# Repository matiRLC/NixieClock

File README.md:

View this project on [CADLAB.io](https://cadlab.io/project/1200). 

# NixieClock
Nixie Tube Clock based project based on existing code and boards by Ogilumen and RobotPirate

The current project uses an Arduino Uno and the Arduinix Shield from RobotPirate. The code is an extension of the sample code
provided by the latter. The PCB for 6 nixie tubes was designed based on the .pdf schematic available in [Arduinix](http://www.arduinix.com).

As of 2019, the current design uses a bluetooth module (HC-06 or HM-10). The use of HM-10 was chosen since it's a Bluetooth 4.0+ module that allows it to work with both Android and iOS apps.

The iOS app was implemented with the work from [hoiberg](https://github.com/hoiberg/HM10-BluetoothSerial-iOS) as a template. His explanation of his project can be found [here](http://www.hangar42.nl/hm10).

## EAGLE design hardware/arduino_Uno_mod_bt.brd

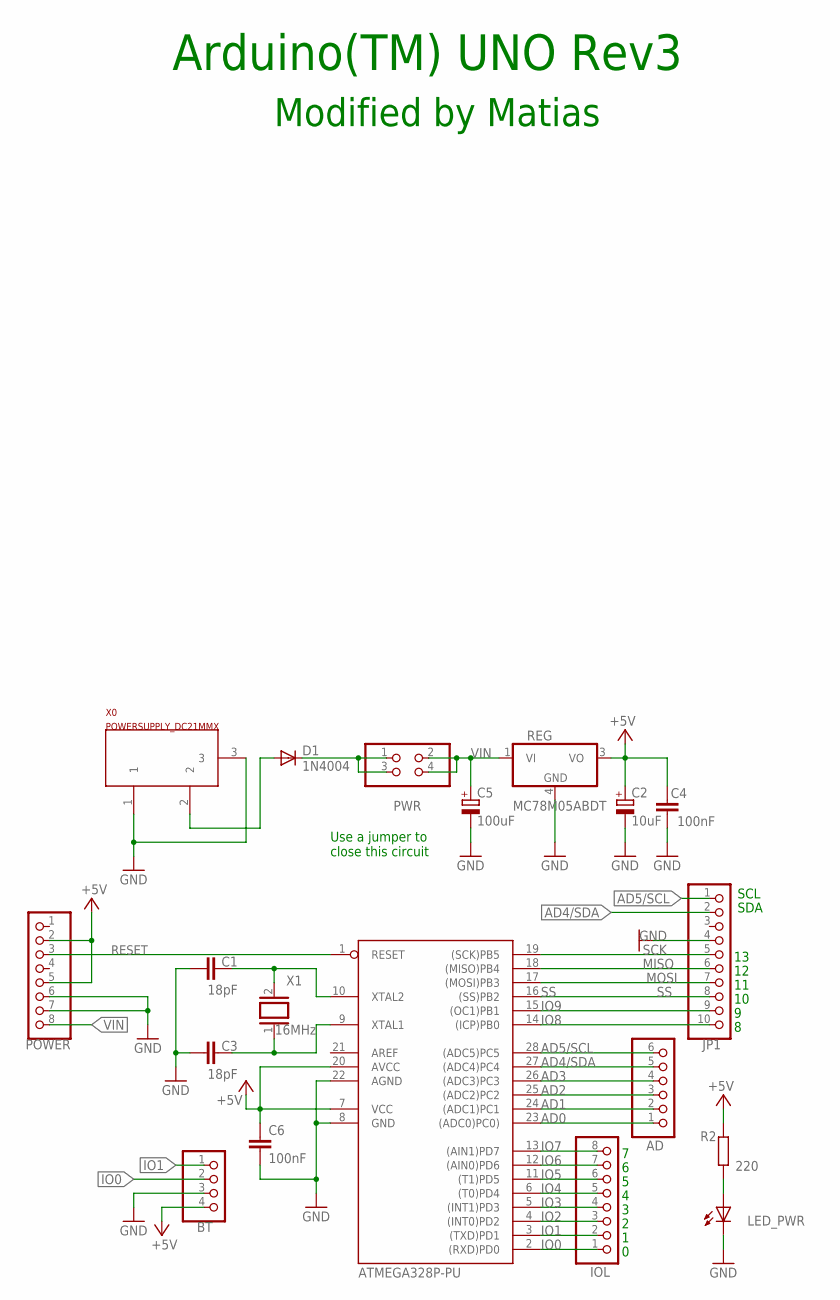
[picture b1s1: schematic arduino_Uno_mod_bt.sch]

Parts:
AD: 6x1F-H8.5; 1X06
BT: PINHD-1X4/90; 1X04/90
C1, C3: 18pF; C025-025X050
C2: 10uF; E2,5-5
C4, C6: 100nF; C025-025X050
C5: 100uF; E2-5
D1: 1N4004; DO41-10
IOL: 8x1F-H8.5; 1X08
JP1: PINHD-1X10; 1X10
LED_PWR: LED3MM
POWER: 8x1F-H8.5; 1X08
PWR: PINHD-2X2; 2X02
R2: 220; R1206
REG: MC78M05ABDT; DPACK_3
X0: POWERSUPPLY_DC21MMX; POWERSUPPLY_DC-21MM
X1: 16MHz; QS
ZU4: ATMEGA328P-PU; DIL28-3

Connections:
+5V: BT.4, C2.+, C4.2, C6.1, POWER.2, POWER.5, R2.2, REG.3 (VO), ZU4.7 (VCC), ZU4.20 (AVCC)
AD0: AD.1, ZU4.23 ((ADC0)PC0))
AD1: AD.2, ZU4.24 ((ADC1)PC1)
AD2: AD.3, ZU4.25 ((ADC2)PC2)
AD3: AD.4, ZU4.26 ((ADC3)PC3)
AD4/SDA: AD.5, JP1.2, ZU4.27 ((ADC4)PC4)
AD5/SCL: AD.6, JP1.1, ZU4.28 ((ADC5)PC5)
GND: BT.3, C1.1, C2.-, C3.1, C4.1, C5.-, C6.2, JP1.4, LED_PWR.K (C), POWER.6, POWER.7, REG.4 (GND), X0.1, X0.3, ZU4.8 (GND), ZU4.22 (AGND)
IN: D1.A, X0.2
IO0: BT.2, IOL.1, ZU4.2 ((RXD)PD0)
IO1: BT.1, IOL.2, ZU4.3 ((TXD)PD1)
IO2: IOL.3, ZU4.4 ((INT0)PD2)
IO3: IOL.4, ZU4.5 ((INT1)PD3)
IO4: IOL.5, ZU4.6 ((T0)PD4)
IO5: IOL.6, ZU4.11 ((T1)PD5)
IO6: IOL.7, ZU4.12 ((AIN0)PD6)
IO7: IOL.8, ZU4.13 ((AIN1)PD7)
IO8: JP1.10, ZU4.14 ((ICP)PB0)
IO9: JP1.9, ZU4.15 ((OC1)PB1)
MISO: JP1.6, ZU4.18 ((MISO)PB4)
MOSI: JP1.7, ZU4.17 ((MOSI)PB3)
unnamed: C3.2, X1.1, ZU4.9 (XTAL1)
unnamed: LED_PWR.A, R2.1
unnamed: D1.C, PWR.1, PWR.3
RESET: POWER.3, ZU4.1 (RESET)
SCK: JP1.5, ZU4.19 ((SCK)PB5)
SS: JP1.8, ZU4.16 ((SS)PB2)
VIN: C5.+, POWER.8, PWR.2, PWR.4, REG.1 (VI)
XTAL2: C1.2, X1.2, ZU4.10 (XTAL2)

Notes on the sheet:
Arduino(TM) UNO Rev3
SDA
SCL
Modified by Matias
Use a jumper to close this circuit

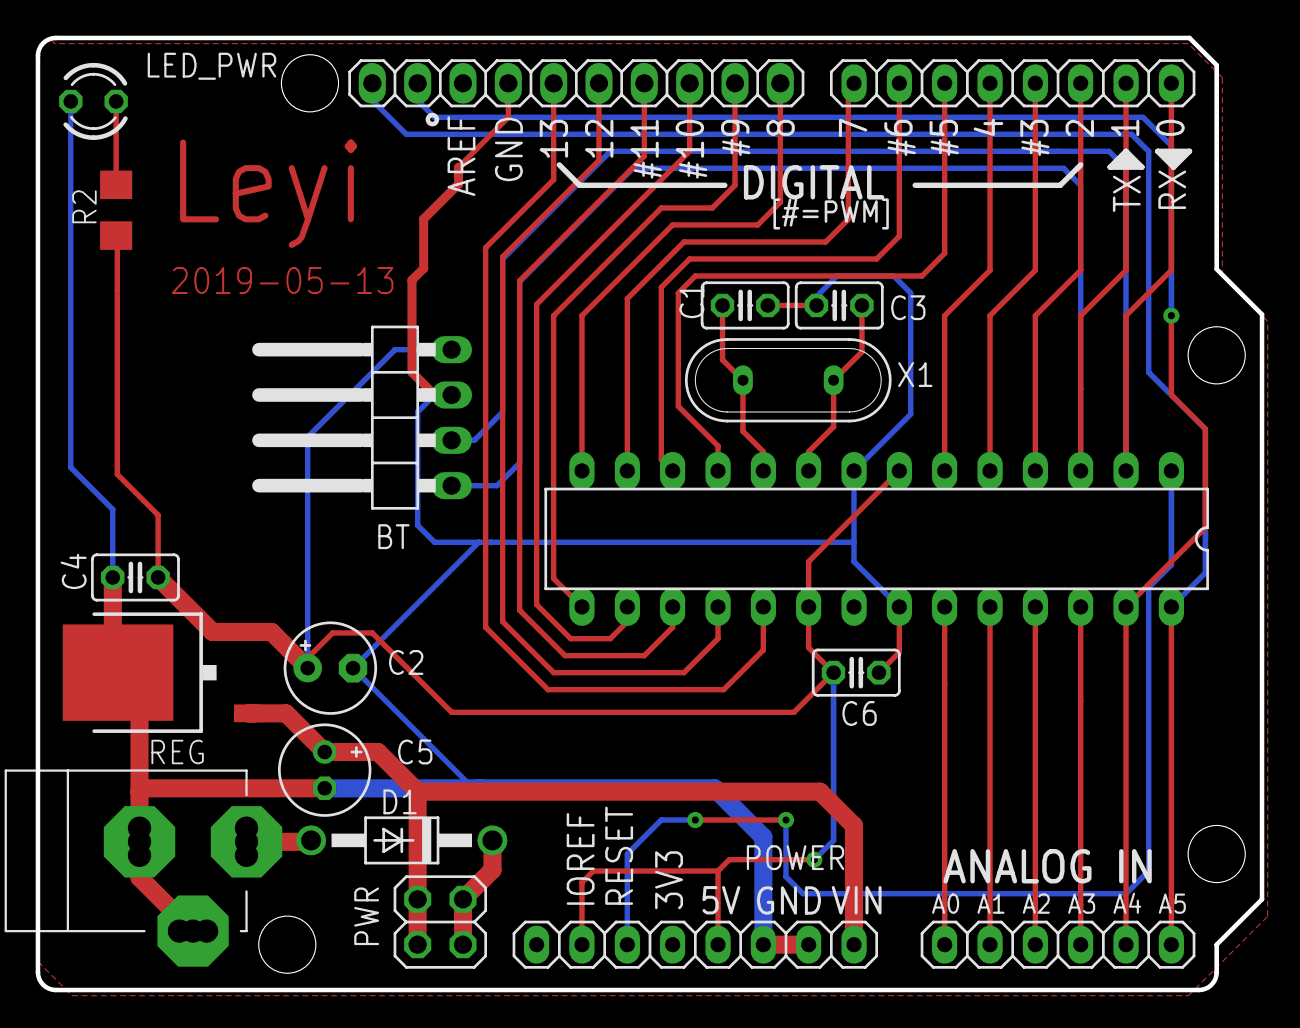
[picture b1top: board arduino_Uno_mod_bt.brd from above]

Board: 2 copper layers, 68.6 x 53.3 mm, 19 parts (0 on the bottom side), 29 nets.

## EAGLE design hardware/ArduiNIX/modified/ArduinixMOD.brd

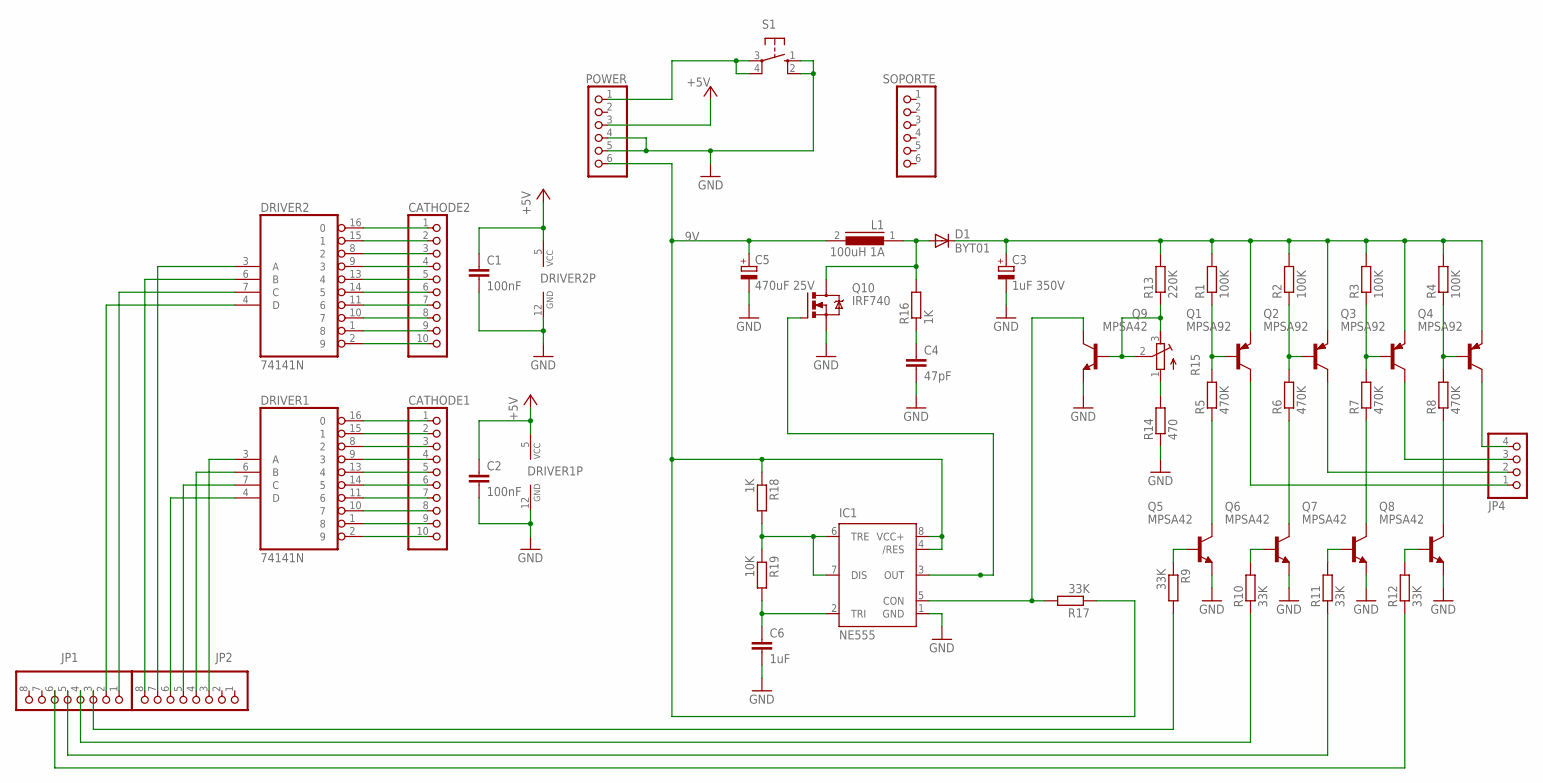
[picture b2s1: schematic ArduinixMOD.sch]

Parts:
C1, C2: 100nF; C025-025X050
C3: 1uF 350V; E2,5-7
C4: 47pF; C025-025X050
C5: 470uF 25V; E5-10,5
C6: 1uF; C025-025X050
CATHODE1, CATHODE2: PINHD-1X10; 1X10
D1: BYT01; F126-10
DRIVER1, DRIVER2: 74141N; DIL16
IC1: NE555; DIL-08
JP1, JP2: PINHD-1X8; 1X08
JP4: PINHD-1X4; 1X04
L1: 100uH 1A; MESC26
POWER: PINHD-1X6; 1X06
Q1, Q2, Q3, Q4: MPSA92; TO92-CBE
Q5, Q6, Q7, Q8, Q9: MPSA42; TO92-EBC
Q10: IRF740; TO220BV
R1, R2, R3, R4: 100K; R1206
R5, R6, R7, R8: 470K; R1206
R9, R10, R11, R12, R17: 33K; R1206
R13: 220K; R1206
R14: 470; R1206
R15: R-TRIMM64W; RTRIM64W
R16, R18: 1K; R1206
R19: 10K; R1206
S1: 10-XX; B3F-10XX
SOPORTE: PINHD-1X6; 1X06

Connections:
9V: C5.+, IC1.4 (/RES), IC1.8 (VCC+), L1.2, POWER.6, R17.1, R18.1
+5V: C1.1, C2.1, DRIVER1.5 (VCC), DRIVER2.5 (VCC), POWER.3
GND: C1.2, C2.2, C3.-, C4.2, C5.-, C6.2, DRIVER1.12 (GND), DRIVER2.12 (GND), IC1.1 (GND), POWER.4, POWER.5, Q5.E, Q6.E, Q7.E, Q8.E, Q9.E, Q10.S, R14.1, S1.1 (S), S1.2 (S1)
unnamed: CATHODE2.9, DRIVER2.1 (8)
unnamed: CATHODE2.10, DRIVER2.2 (9)
unnamed: DRIVER2.3 (A), JP2.7
unnamed: DRIVER2.4 (D), JP1.2
unnamed: DRIVER2.6 (B), JP2.8
unnamed: DRIVER2.7 (C), JP1.1
unnamed: CATHODE2.3, DRIVER2.8 (2)
unnamed: CATHODE2.4, DRIVER2.9 (3)
unnamed: CATHODE2.8, DRIVER2.10 (7)
unnamed: CATHODE2.7, DRIVER2.11 (6)
unnamed: DRIVER1.4 (D), JP2.6
unnamed: CATHODE2.5, DRIVER2.13 (4)
unnamed: CATHODE2.6, DRIVER2.14 (5)
unnamed: CATHODE2.2, DRIVER2.15 (1)
unnamed: CATHODE2.1, DRIVER2.16 (0)
unnamed: DRIVER1.6 (B), JP2.4
unnamed: DRIVER1.7 (C), JP2.5
unnamed: CATHODE1.3, DRIVER1.8 (2)
unnamed: CATHODE1.9, DRIVER1.1 (8)
unnamed: CATHODE1.10, DRIVER1.2 (9)
unnamed: DRIVER1.3 (A), JP2.3
unnamed: CATHODE1.4, DRIVER1.9 (3)
unnamed: CATHODE1.8, DRIVER1.10 (7)
unnamed: CATHODE1.7, DRIVER1.11 (6)
unnamed: CATHODE1.5, DRIVER1.13 (4)
unnamed: CATHODE1.6, DRIVER1.14 (5)
unnamed: CATHODE1.2, DRIVER1.15 (1)
unnamed: CATHODE1.1, DRIVER1.16 (0)
unnamed: Q1.B, R1.1, R5.2
unnamed: Q2.B, R2.1, R6.2
unnamed: Q3.B, R3.1, R7.2
unnamed: Q4.B, R4.1, R8.2
unnamed: D1.A, L1.1, Q10.D, R16.2
unnamed: JP4.2, Q2.C
unnamed: JP1.3, R9.2
unnamed: JP4.1, Q1.C
unnamed: JP1.4, R10.1
unnamed: JP4.3, Q3.C
unnamed: JP4.4, Q4.C
unnamed: Q5.C, R5.1
unnamed: Q6.C, R6.1
unnamed: Q5.B, R9.1
unnamed: Q6.B, R10.2
unnamed: Q7.B, R11.2
unnamed: Q7.C, R7.1
unnamed: Q8.C, R8.1
unnamed: Q8.B, R12.2
unnamed: JP1.5, R11.1
unnamed: JP1.6, R12.1
unnamed: Q9.B, R13.1, R15.2 (S), R15.3 (E)
unnamed: C4.1, R16.1
unnamed: R14.2, R15.1 (A)
unnamed: C3.+, D1.C, Q1.E, Q2.E, Q3.E, Q4.E, R1.2, R2.2, R3.2, R4.2, R13.2
unnamed: IC1.6 (TRE), IC1.7 (DIS), R18.2, R19.1
unnamed: C6.1, IC1.2 (TRI), R19.2
unnamed: POWER.1, S1.3, S1.4 (P1)
unnamed: IC1.5 (CON), Q9.C, R17.2
unnamed: IC1.3 (OUT), Q10.G

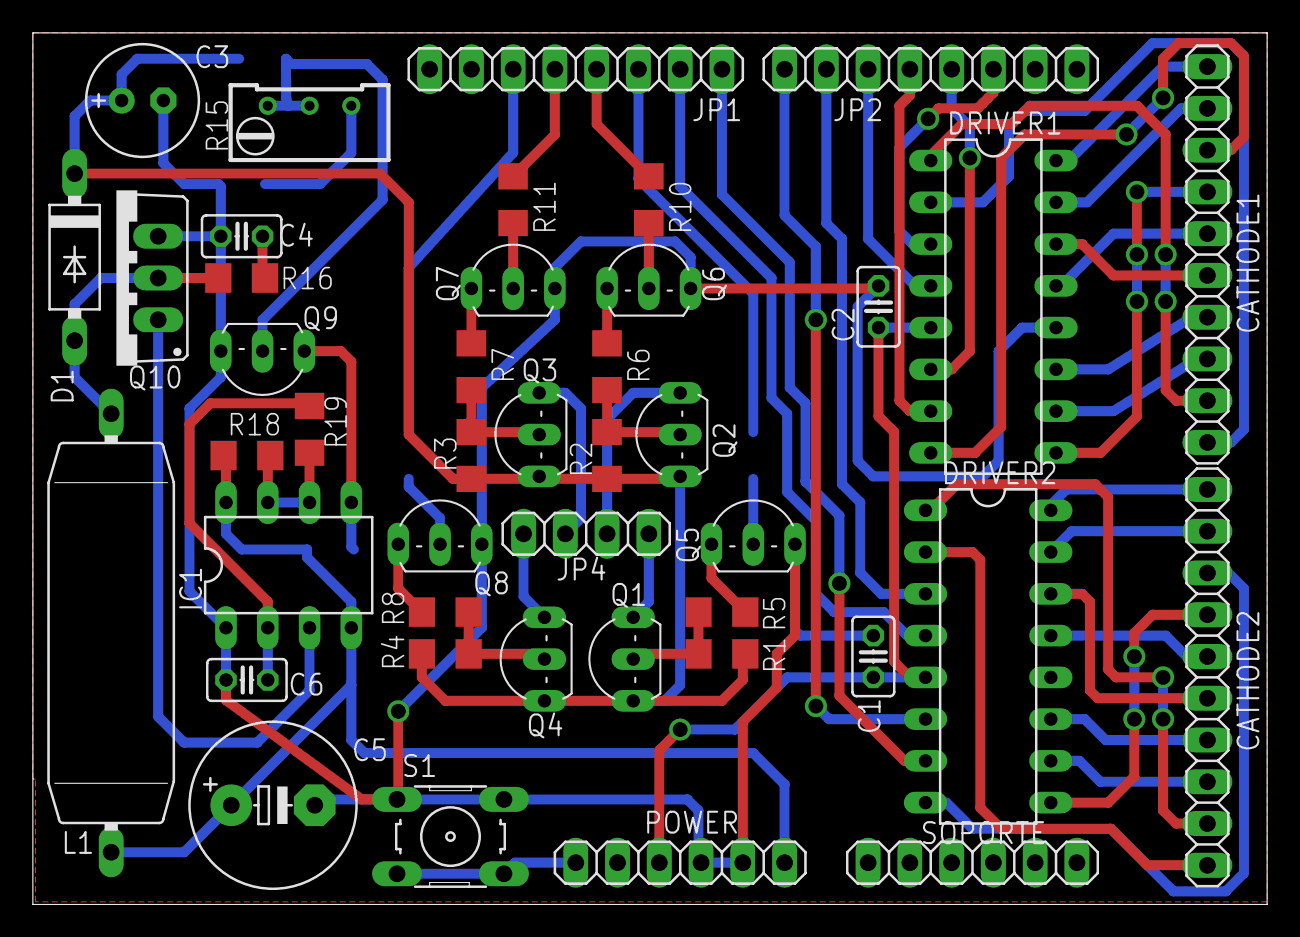
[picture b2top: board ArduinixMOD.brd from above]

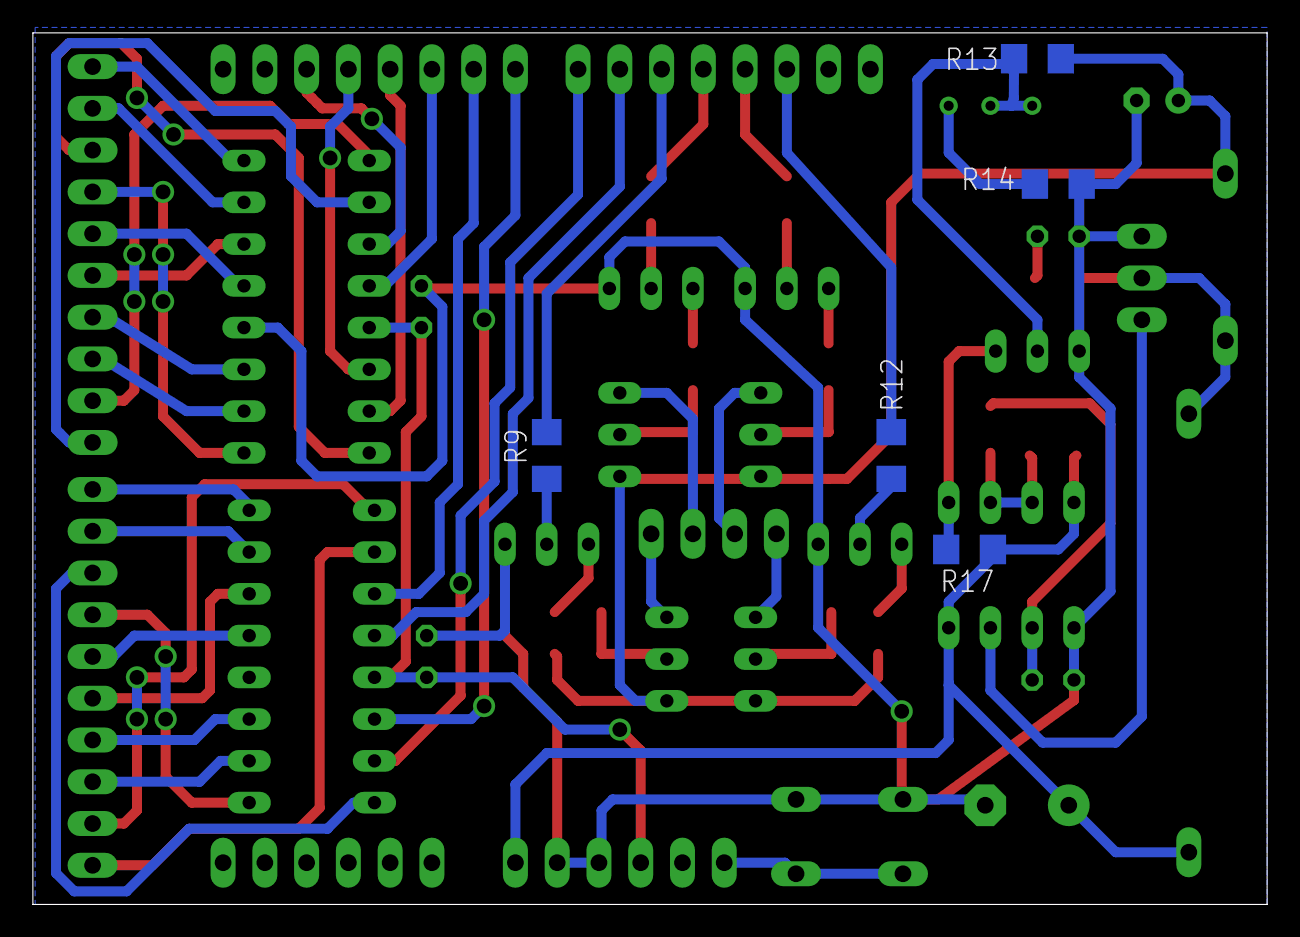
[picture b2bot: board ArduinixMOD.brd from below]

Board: 2 copper layers, 75.1 x 53.0 mm, 48 parts (5 on the bottom side), 61 nets.

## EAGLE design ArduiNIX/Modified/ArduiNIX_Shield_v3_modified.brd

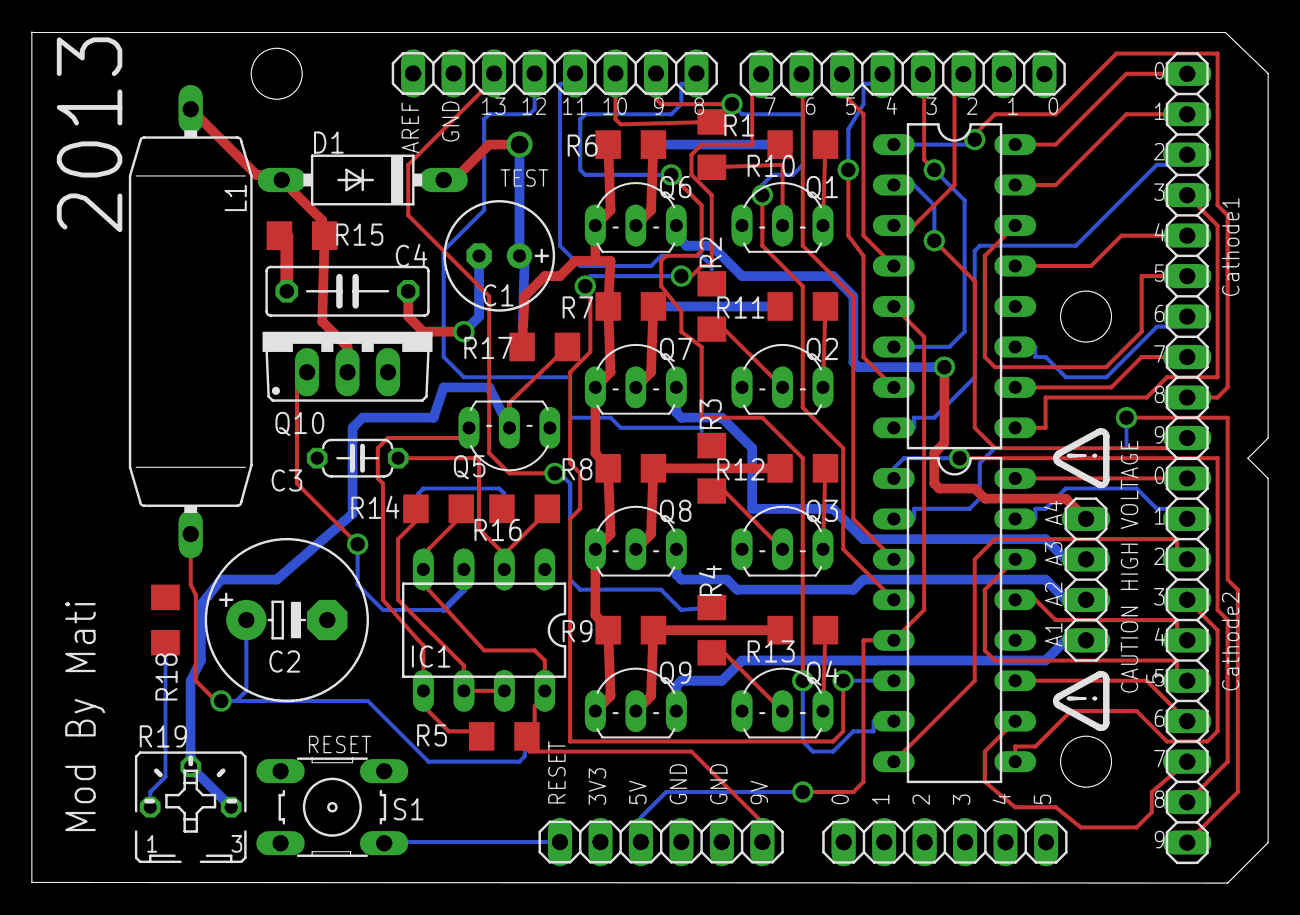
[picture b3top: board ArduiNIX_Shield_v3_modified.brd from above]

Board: 2 copper layers, 77.6 x 53.4 mm, 46 parts (0 on the bottom side), 61 nets.

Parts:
C1: 1uF 350v; E2,5-7
C2: 470uF 25v; E5-10,5
C3: 2n2; C050-024X044
C4: 47pF; C075-032X103
CATHODE1, CATHODE2: 1X10
D1: BYT01; F126-10
DRIVER1, DRIVER2: 74141N; DIL16
IC1: NE555; DIL-08
J1, J3: 1X08
J2: 1X06
JP2: 1X04
JP3: 1X06
L1: 100uH 1A; MESC26
Q1, Q2, Q3, Q4, Q5: MPSA42; TO92-CBE
Q6, Q7, Q8, Q9: MPSA92; TO92-CBE
Q10: IRF740; TO220BV
R1, R2, R3, R4, R5: 33k; R1206
R6, R7, R8, R9: 100k; R1206
R10, R11, R12, R13: 470k; R1206
R14, R15: 1k; R1206
R16: 10k; R1206
R17: 220k; R1206
R18: 470; R1206
R19: B25P
S1: B3F-10XX

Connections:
5V: DRIVER1.5, DRIVER2.5, JP3.3
GND: C1.-, C2.-, C3.2, C4.2, DRIVER1.12, DRIVER2.12, IC1.1, JP3.4, JP3.5, Q1.E, Q2.E, Q3.E, Q4.E, Q5.E, Q10.S, R18.1, S1.2
unnamed: CATHODE2.2, DRIVER2.15
unnamed: Q6.B, R6.1, R10.2
unnamed: CATHODE2.3, DRIVER2.8
unnamed: DRIVER1.3, J1.3
unnamed: DRIVER1.6, J1.4
unnamed: DRIVER1.7, J1.5
unnamed: CATHODE1.10, DRIVER1.2
unnamed: C4.1, R15.1
unnamed: DRIVER2.6, J1.8
unnamed: DRIVER2.7, J3.1
unnamed: DRIVER2.3, J1.7
unnamed: CATHODE2.4, DRIVER2.9
unnamed: CATHODE2.5, DRIVER2.13
unnamed: CATHODE2.6, DRIVER2.14
unnamed: CATHODE2.7, DRIVER2.11
unnamed: CATHODE2.8, DRIVER2.10
unnamed: CATHODE2.9, DRIVER2.1
unnamed: CATHODE2.10, DRIVER2.2
unnamed: C1.+, D1.C, Q6.E, Q7.E, Q8.E, Q9.E, R6.2, R7.2, R8.2, R9.2, R17.2
unnamed: CATHODE1.2, DRIVER1.15
unnamed: CATHODE1.6, DRIVER1.14
unnamed: CATHODE2.1, DRIVER2.16
unnamed: DRIVER2.4, J3.2
unnamed: DRIVER1.4, J1.6
unnamed: CATHODE1.4, DRIVER1.9
unnamed: CATHODE1.8, DRIVER1.10
unnamed: CATHODE1.7, DRIVER1.11
unnamed: CATHODE1.5, DRIVER1.13
unnamed: CATHODE1.9, DRIVER1.1
unnamed: Q1.B, R1.1
unnamed: Q2.B, R2.1
unnamed: Q3.B, R3.1
unnamed: J3.3, R1.2
unnamed: J3.4, R2.2
unnamed: J3.5, R3.2
unnamed: Q1.C, R10.1
unnamed: Q2.C, R11.1
unnamed: Q3.C, R12.1
unnamed: JP2.1, Q6.C
unnamed: JP2.2, Q7.C
unnamed: JP2.3, Q8.C
unnamed: Q7.B, R7.1, R11.2
unnamed: Q8.B, R8.1, R12.2
unnamed: CATHODE1.3, DRIVER1.8
unnamed: D1.A, L1.1, Q10.D, R15.2
unnamed: Q5.B, R17.1, R19.E, R19.S
unnamed: R18.2, R19.A
unnamed: Q9.B, R9.1, R13.2
unnamed: IC1.6, IC1.7, R14.1, R16.2
unnamed: JP2.4, Q9.C
unnamed: JP3.1, S1.4
unnamed: IC1.3, Q10.G
unnamed: IC1.5, Q5.C, R5.1
unnamed: C3.1, IC1.2, R16.1
unnamed: Q4.C, R13.1
unnamed: Q4.B, R4.1
unnamed: J3.6, R4.2
unnamed: CATHODE1.1, DRIVER1.16
VCC: C2.+, IC1.4, IC1.8, JP3.6, L1.2, R5.2, R14.2

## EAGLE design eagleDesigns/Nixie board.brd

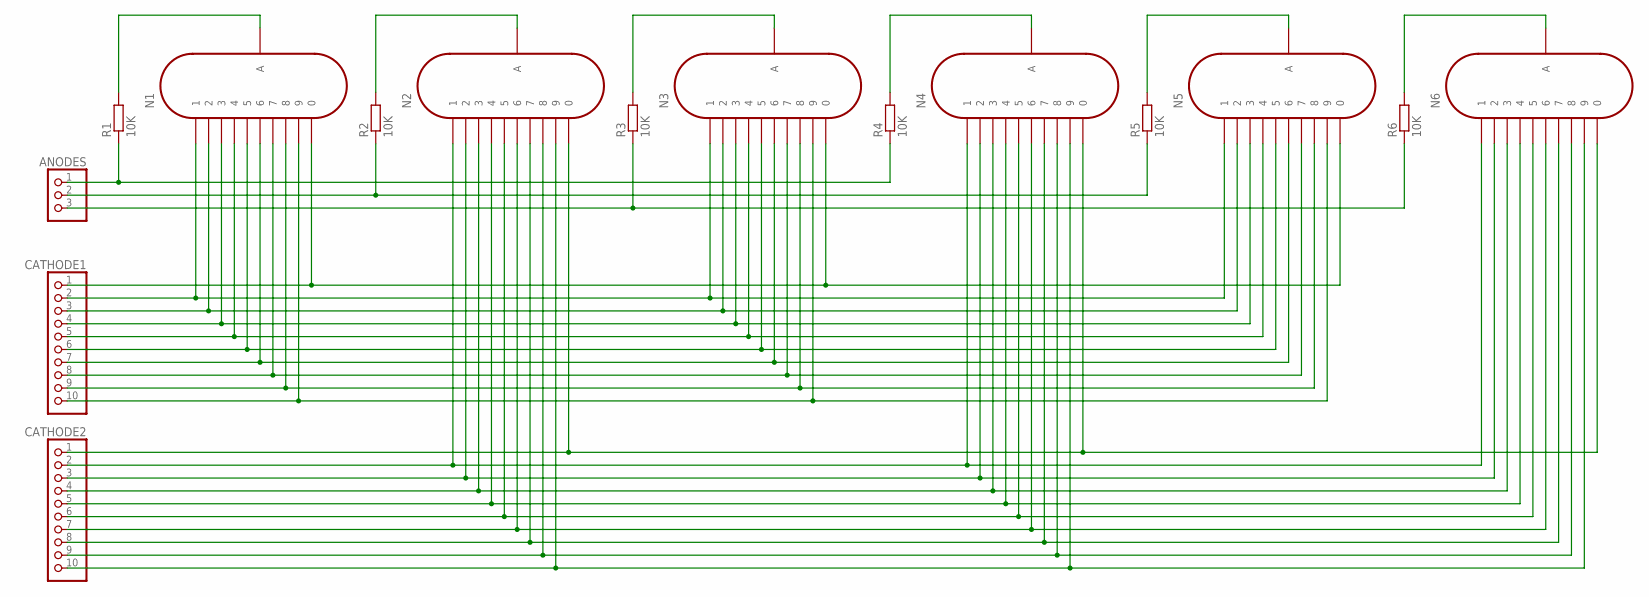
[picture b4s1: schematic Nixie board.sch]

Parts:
ANODES: PINHD-1X3; 1X03
CATHODE1, CATHODE2: PINHD-1X10; 1X10
N1, N2, N3, N4, N5, N6: IN-12A; IN-12
R1, R2, R3, R4, R5, R6: 10K; 0207/10

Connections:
unnamed: N1.A, R1.2
unnamed: ANODES.1, R1.1, R4.1
unnamed: N4.A, R4.2
unnamed: ANODES.2, R2.1, R5.1
unnamed: N5.A, R5.2
unnamed: N2.A, R2.2
unnamed: ANODES.3, R3.1, R6.1
unnamed: N6.A, R6.2
unnamed: N3.A, R3.2
unnamed: CATHODE1.1, N1.0, N3.0, N5.0
unnamed: CATHODE1.2, N1.1, N3.1, N5.1
unnamed: CATHODE1.3, N1.2, N3.2, N5.2
unnamed: CATHODE1.4, N1.3, N3.3, N5.3
unnamed: CATHODE1.5, N1.4, N3.4, N5.4
unnamed: CATHODE1.6, N1.5, N3.5, N5.5
unnamed: CATHODE1.7, N1.6, N3.6, N5.6
unnamed: CATHODE1.8, N1.7, N3.7, N5.7
unnamed: CATHODE1.9, N1.8, N3.8, N5.8
unnamed: CATHODE1.10, N1.9, N3.9, N5.9
unnamed: CATHODE2.1, N2.0, N4.0, N6.0
unnamed: CATHODE2.2, N2.1, N4.1, N6.1
unnamed: CATHODE2.3, N2.2, N4.2, N6.2
unnamed: CATHODE2.4, N2.3, N4.3, N6.3
unnamed: CATHODE2.5, N2.4, N4.4, N6.4
unnamed: CATHODE2.6, N2.5, N4.5, N6.5
unnamed: CATHODE2.7, N2.6, N4.6, N6.6
unnamed: CATHODE2.8, N2.7, N4.7, N6.7
unnamed: CATHODE2.9, N2.8, N4.8, N6.8
unnamed: CATHODE2.10, N2.9, N4.9, N6.9

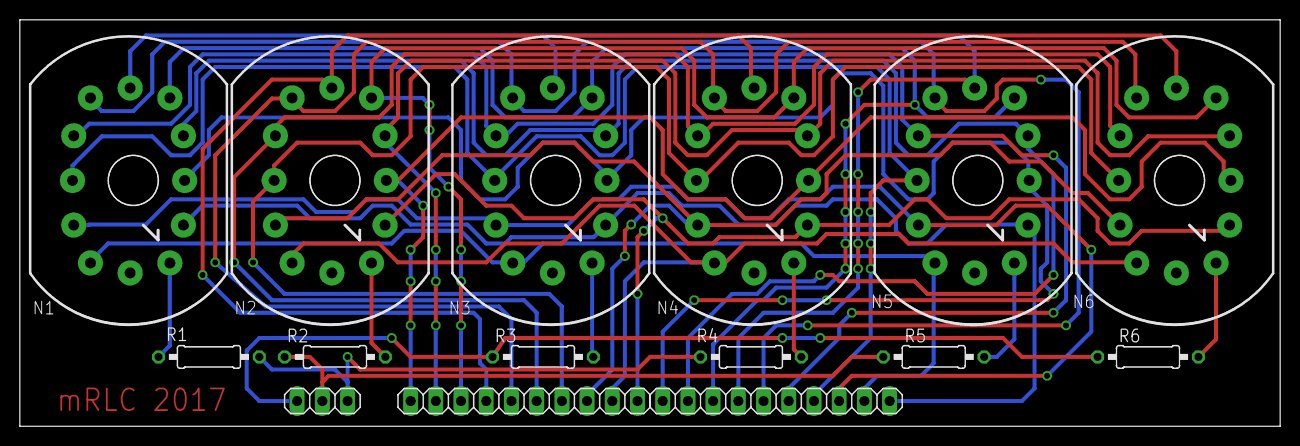
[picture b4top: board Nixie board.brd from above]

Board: 2 copper layers, 127.0 x 40.9 mm, 15 parts (0 on the bottom side), 29 nets.

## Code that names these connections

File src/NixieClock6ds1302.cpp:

/**
 * Arduinix 6 Bulb ( IN-17 ) 
 * - Also supports Hour and Min. time set.
 *
 * This code runs a six bulb setup and displays a prototype clock setup.
 * NOTE: the delay is setup for IN-17 nixie bulbs.
 * by Jeremy Howa
 * www.robotpirate.com
 * www.arduinix.com
 * 2008 - 2009
 * Last Edit Aug 29, 2009
 *
 * NOTE: Major changes were basically formatting and pin selection based on my
 *       own PCB for the nixie tubes (NH-12A)
 * @author Matias Quintana matiasquitana.com
 * @version 16/01/17
 */

/**
 * SN74141: True Table
 * D  C  B  A  #     
 * L, L, L, L  0
 * L, L, L, H  1
 * L, L, H, L  2
 * L, L, H, H  3
 * L, H, L, L  4
 * L, H, L, H  5
 * L, H, H, L  6
 * L, H, H, H  7
 * H, L, L, L  8
 * H, L, L, H  9
 */

// Debug mode for sending the current time via serial 
#define DEBUG_ON true

/** Pin mapping for ADC, Arduino UNO, Atmega328P
 * ARDUINO UNO    Atmega328P
 *     PIN2          PD2
 *     PIN3          PD3
 *     PIN4          PD4
 *     PIN5          PD5
 *     PIN6          PD6
 *     PIN7          PD7
 *     PIN8          PB0
 *     PIN9          PB1
 *    PIN10          PB2
 *    PIN11          PB3
 *    PIN12          PB4
 *    PIN14          PC0
 *    PIN15          PC1
 */

/**
 * setup()
 * Purpose: IO initialization and debugging flag set
 */
void setup() {
    // SN74141 (1)
    // Output: PD2:PD5
    // PD2 = a, PD3 = b, PD4 = c, PD5 = d
    DDRD |= 0b11111100;
    // SN74141 (2)
    // Output: PD6:PD7 and PB0:PB1
    // PD6 = a, PD7 = b, PB0 = c, PB1 = d
    DDRB |= 0b00011111;
    // Anode pins:PB2:PB4
    // PB2: anode1
    // PB3: anode2
    // PB4: anode3

    // The following pins can be wired to buttons
    // Grounding on pins PC0 and PC1 will set the Hour and Mins.
    // Input: PC0:PC1
    DDRC |= 0b00000000;
    // Set pull up resistors in those pins
    PORTC |= 0b00000011;  
  
    if (DEBUG_ON) {
        Serial.begin(9600);
    }
}

/**
 * DisplayNumberSet
 * Purpose: Looks up the truth table and opens the correct outs from the arduino
 * to light the numbers given to this funciton (num1,num2), on a 6 nixie bulb setup. 
 * @var anod anode number
 * @var num1 bulb 1 value
 * @var num2 bulb 2 value
 **/
void DisplayNumberSet (int anod, int num1, int num2) {
    int a,b,c,d;

    // set defaults.
    a = 0; b = 0; c = 0; d = 0; // will display a zero.
  
    // Load the a,b,c,d.. to send to the SN74141 IC (1)
    switch (num1) {
        case 0: a = 0; b = 0; c = 0; d = 0; break;
        case 1: a = 1; b = 0; c = 0; d = 0; break;
        case 2: a = 0; b = 1; c = 0; d = 0; break;
        case 3: a = 1; b = 1; c = 0; d = 0; break;
        case 4: a = 0; b = 0; c = 1; d = 0; break;
        case 5: a = 1; b = 0; c = 1; d = 0; break;
        case 6: a = 0; b = 1; c = 1; d = 0; break;
        case 7: a = 1; b = 1; c = 1; d = 0; break;
        case 8: a = 0; b = 0; c = 0; d = 1; break;
        case 9: a = 1; b = 0; c = 0; d = 1; break;
    }    
    
    // Write the value in SN74141 (1)
    // set nth bit to value x
    // number = number & ~(1 << n) | (x << n);
    PORTD = PIND & ~(1 << PD5) | (d << PD5); // d
    PORTD = PIND & ~(1 << PD4) | (c << PD4); // c
    PORTD = PIND & ~(1 << PD3) | (b << PD3); // b
    PORTD = PIND & ~(1 << PD2) | (a << PD2); // a

    // Load the a,b,c,d.. to send to the SN74141 IC (2)
    switch (num2) {
        case 0: a = 0; b = 0; c = 0; d = 0; break;
        case 1: a = 1; b = 0; c = 0; d = 0; break;
        case 2: a = 0; b = 1; c = 0; d = 0; break;
        case 3: a = 1; b = 1; c = 0; d = 0; break;
        case 4: a = 0; b = 0; c = 1; d = 0; break;
        case 5: a = 1; b = 0; c = 1; d = 0; break;
        case 6: a = 0; b = 1; c = 1; d = 0; break;
        case 7: a = 1; b = 1; c = 1; d = 0; break;
        case 8: a = 0; b = 0; c = 0; d = 1; break;
        case 9: a = 1; b = 0; c = 0; d = 1; break;
    }

    // Write the value in SN74141 (2)
    PORTB = PINB & ~(1 << PB1) | (d << PB1); // d
    PORTB = PINB & ~(1 << PB0) | (c << PB0); // c
    PORTD = PIND & ~(1 << PD7) | (b << PD7); // b
    PORTD = PIND & ~(1 << PD6) | (a << PD6); // a

    // Select what node to fire and turn on that node (HIGH)
    switch (anod) {
        case 0: PORTB |= 1 << PB2; break;
        case 1: PORTB |= 1 << PB3; break;
        case 2: PORTB |= 1 << PB4; break;
    }

    // Delay
    // NOTE: With the differnce in Nixie bulbs you may have to change
    //       this delay to set the update speed of the bulbs. If you 
    //       dont wait long enough the bulb will be dim or not light at all
    //       you want to set this delay just right so that you have 
    //       nice bright output yet quick enough so that you can multiplex with
    //       more bulbs.
    delay(2);
  
    switch (anod) { // Turn off this anode (LOW)
        case 0: PORTB &= ~(1 << PB2); break;
        case 1: PORTB &= ~(1 << PB3); break;
        case 2: PORTB &= ~(1 << PB4); break;
    }
}

/**
 * DisplayNumberString
 * Purpose: passing an array that is 8 elements long will display numbers
 *          on a 6 nixie bulb setup.
 * @var array int* array containing the values for all 6 nixie tubes
 */
void DisplayNumberString (int* array) {
    // bank 1 (bulb 0, 3)
    DisplayNumberSet(0, array[0], array[3]);
    // bank 2 (bulb 1, 4)
    DisplayNumberSet(1, array[4], array[1]); //it should be (1, array[1], array[4]) but there was a mistake in the first PCB
    // bank 3 (bulb 2, 5)
    DisplayNumberSet(2, array[2], array[5]);   
}

// DEFINE
long MINS  = 60;         // 60 Seconds in a Min.
long HOURS = 60 * MINS;  // 60 Mins in an hour.
long DAYS  = 12 * HOURS; // 24 Hours in a day. > Note: change the 24 to a 12 for non millitary time.

long runTime = 0;        // Time from when we started.

// default time sets. clock will start at the indicated values below clockHourSet:clockMinSet:00
// NOTE: Seconds start at 0
long clockHourSet = 12;
long clockMinSet  = 34;

int HourButtonPressed = false;
int MinButtonPressed = false;

/**
 * Loop
 * Purpose: Main function that will continue to be executed as long as the system is energised
 */
void loop() {
    // Get milliseconds.
    runTime = millis();

    // Get time in seconds.
    long time = (runTime) / 1000;

    int hourInput = PINC & 0x01; // PC0
    int minInput = PINC & 0x02;  // PC1
      
    if(DEBUG_ON)
        Serial.println( hourInput );       
  
    if(hourInput == 0)
        HourButtonPressed = true;

    if(minInput == 0)
        MinButtonPressed = true;
  
    if(HourButtonPressed == true && hourInput == 1) {
        clockHourSet++;
        HourButtonPressed = false;
    }
  
    if(MinButtonPressed == true && minInput == 1) {
        clockMinSet++;
        MinButtonPressed = false;
    }
  
    // Set time based on offset..
    long hbump = 60 * 60 * clockHourSet;
    long mbump = 60 * clockMinSet;
    time += mbump + hbump;

    // Convert time to days,hours,mins,seconds
    long days  = time / DAYS;       time -= days  * DAYS; 
    long hours = time / HOURS;      time -= hours * HOURS; 
    long minutes  = time / MINS;    time -= minutes  * MINS; 
    long seconds  = time; 

    // Get the high and low order values for hours,min,seconds. 
    int lowerHours = hours % 10;
    int upperHours = hours - lowerHours;
    int lowerMins = minutes % 10;
    int upperMins = minutes - lowerMins;
    int lowerSeconds = seconds % 10;
    int upperSeconds = seconds - lowerSeconds;
    if (upperSeconds >= 10) upperSeconds = upperSeconds / 10;
    if (upperMins >= 10) upperMins = upperMins / 10;
    if (upperHours >= 10) upperHours = upperHours / 10;

    // Fill in the Number array used to display on the tubes.
    int NumberArray[6] = {0, 0, 0, 0, 0, 0};
    NumberArray[0] = upperHours;
    NumberArray[1] = lowerHours;
    NumberArray[2] = upperMins;
    NumberArray[3] = lowerMins;
    NumberArray[4] = upperSeconds;
    NumberArray[5] = lowerSeconds;

    // Display.
    DisplayNumberString(NumberArray);
}

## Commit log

2017-07-30 First upload of existing files
2018-04-22 added RTC code. Microcontroller can read time from the RTC and use that as baseline for keeping track of time
2018-04-22 rearranged file structures and documents
2018-04-22 modified README
2018-04-22 fixed URL in README
2018-04-22 tweak more with the file structure
2018-04-22 adding stuff to the .gitignore
2018-04-22 fixing .gitignore
2018-05-27 rearranged file structures and added files to .gitignore
2018-06-26 Backlink to CADLAB.io has been added.
2018-07-06 finished mobile app to set hour through bluetooth. Added bluetooth portion into the microcontroller code section
2018-07-06 sorted pictures out
2018-12-29 added only bluetooth version
2019-01-03 rebuild app
2019-01-11 testing android app, but need HC05
2019-02-04 colon and BT script updated
2019-02-06 dots and BT script updated. Starting iOS version
2019-03-12 updated android app to handle BLE 4.0
2019-03-21 updated README.md and iOS app
2019-03-24 new title
2019-04-16 playing with delay options
2019-04-17 change delay times for bulbs
